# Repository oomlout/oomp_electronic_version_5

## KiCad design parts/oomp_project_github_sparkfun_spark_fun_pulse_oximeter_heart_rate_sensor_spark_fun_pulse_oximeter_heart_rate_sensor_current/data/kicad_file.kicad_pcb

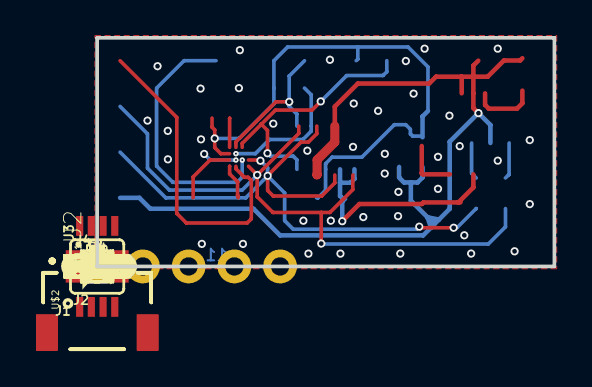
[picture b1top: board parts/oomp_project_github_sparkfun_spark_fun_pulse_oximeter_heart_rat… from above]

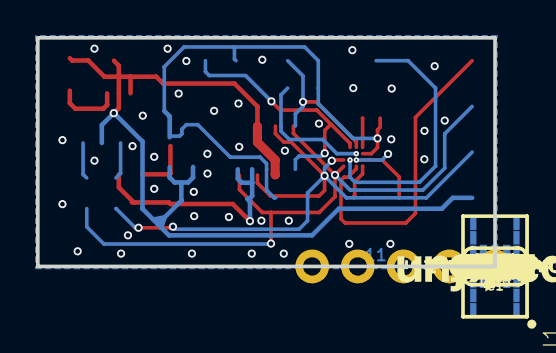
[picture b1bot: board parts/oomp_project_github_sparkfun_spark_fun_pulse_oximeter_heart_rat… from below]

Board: 2 copper layers, 25.4 x 12.7 mm, 50 parts (24 on the bottom side), 18 nets.

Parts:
C1, C3: 10uF; 0603
C2: 0.1uF; 0402-TIGHT
C4: 22uF; 0805
C5: 1.0uF; 0603
C6, C7: 1.0uF; 0402-TIGHT
FD1, FD2, FD3, FD4: FIDUCIALUFIDUCIAL; FIDUCIAL-MICRO
FRAME1: FRAME-LETTER; CREATIVE_COMMONS
I2C0: JUMPER-SMT_3_2-NC_TRACE_SILK; SMT-JUMPER_3_2-NC_TRACE_SILK
J1, J2: QWIIC_RIGHT_ANGLE; JST04_1MM_RA
J3: 1X05_NO_SILK
J4: 1X01_NO_SILK
L1: 2.2μH; 0806
LOGO1: SFE_LOGO_FLAME.1_INCH; SFE_LOGO_FLAME_.1
LOGO2: OSHW-LOGOMINI; OSHW-LOGO-MINI
LOGO3: SFE_LOGO_NAME.1_INCH; SFE_LOGO_NAME_.1
LOGO4: SPECIAL_INSTRUCTIONS-ORDERING; ORDERING_INSTRUCTIONS
LOGO5: QWIIC_LOGO_4MM; QWIIC_4MM
R1, R2, R5, R6, R7: 4.7k; 0603
R3: 750K; 0603
R4: 100k; 0402-TIGHT
U1: MAX30101EFD; 14_PIN_OESIP
U2: MAX32664GWEA; 16_PIN_WLP
U3: 1.8V/100mA; SC70
U$1: #I2C#1348
U$2: PAM2401; MSOP8
U$3, U$5: #GND#0
U$4: #SCL#7
U$6, U$12: #RST#32
U$7: 3V338
U$8: #SDA#10
U$9: #3V3#1
U$10: #SDA#9
U$11: #SCL#9
U$13: ##MFIO##12
U$17: PULSE35
U$20: OXIMETER_AND36
U$21: HEART_RATE_MONITOR37
Y1: 32.768kHz; CRYSTAL-SMD-3.2X1.5MM

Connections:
1.8V: C2.1, C5.1, C6.1, R1.2, R2.2, R5.2, U1.P11, U2.3, U3.5
3.3V: C3.1, I2C0.2, J1.2, J2.2, J3.2, L1.1, U3.1, U3.3, U$2.2, U$2.3
5V: C1.1, C4.1, R3.2, U1.P9, U1.P10, U$2.7
GND: C1.2, C2.2, C3.2, C4.2, C5.2, C6.2, C7.2, J1.1, J2.1, J3.1, R4.1, U1.P4, U1.P12, U2.13, U3.2, U$2.4, U$2.8
HOST_SCL: J1.4, J2.4, J3.4, R7.1, U2.10
HOST_SDA: J1.3, J2.3, J3.3, R6.1, U2.9
unnamed: C7.1, U2.4
unnamed: R3.1, R4.2, U$2.5
unnamed: L1.2, U$2.1
unnamed: I2C0.3, R6.2
unnamed: I2C0.1, R7.2
unnamed: U2.1, Y1.P$1
unnamed: U2.2, Y1.P$2
SNSR_SCL: R2.1, U1.P2, U2.5
SNSR_SDA: R1.1, U1.P3, U2.14
~HR_INT: R5.1, U1.P13, U2.6
~MFIO: J4.1, U2.16
~RST: J3.5, U2.12

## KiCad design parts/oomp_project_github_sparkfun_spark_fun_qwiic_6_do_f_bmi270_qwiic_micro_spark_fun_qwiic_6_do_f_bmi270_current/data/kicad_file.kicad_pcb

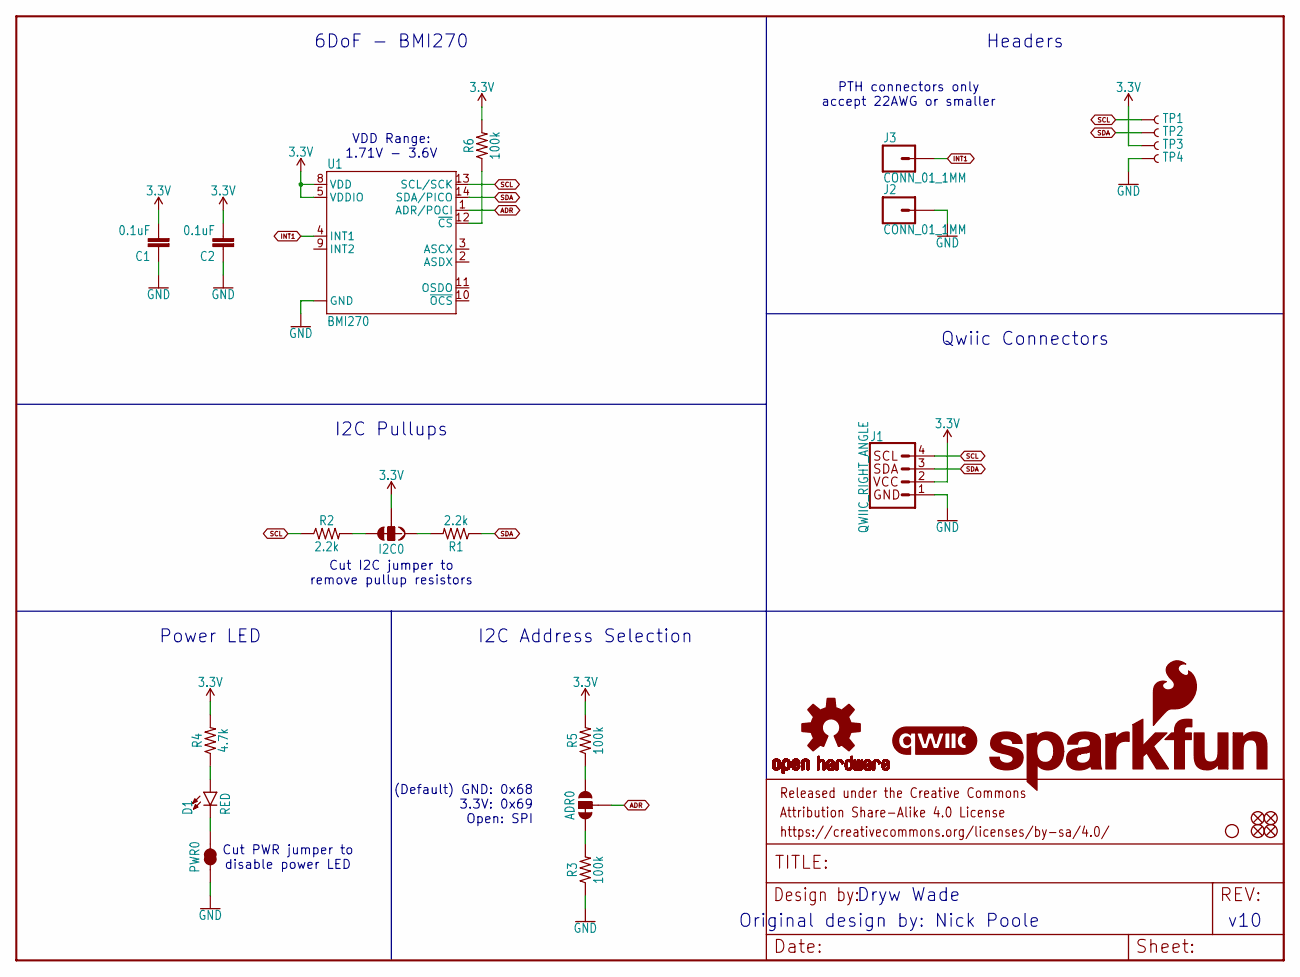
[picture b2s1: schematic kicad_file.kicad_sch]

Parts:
ADR0: JUMPER-SMT_3_1-NC_TRACE_SILK; SMT-JUMPER_3_1-NC_TRACE_SILK
C1, C2: 0.1uF; 0402-TIGHT
D1: RED; LED-0402
FD1, FD2, FD3, FD4: FIDUCIALUFIDUCIAL; FIDUCIAL-MICRO
FRAME1: FRAME-LETTER; CREATIVE_COMMONS
H1: STAND-OFF
I2C0: JUMPER-SMT_3_2-NC_TRACE_SILK; SMT-JUMPER_3_2-NC_TRACE_SILK
J1: QWIIC_RIGHT_ANGLE; JST04_1MM_RA
J2, J3: CONN_01_1MM; 1X01_1MM_NO_SILK
LOGO1: SFE_LOGO_NAME_FLAMEBLANK; BLANK
LOGO2: QWIIC_LOGO_3MM; QWIIC_3MM
LOGO3: OSHW-LOGOMINI; OSHW-LOGO-MINI
PWR0: JUMPER-SMT_2_NC_TRACE_SILK; SMT-JUMPER_2_NC_TRACE_SILK
R1, R2: 2.2k; 0402-TIGHT
R3, R5, R6: 100k; 0402-TIGHT
R4: 4.7k; 0402-TIGHT
TP1, TP2, TP3, TP4: TEST-POINT3; PAD.03X.03
U1: BMI270

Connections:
3.3V: C1.2, C2.2, I2C0.2, J1.2, R4.2, R5.2, R6.2, TP3.1, U1.5 (VDDIO), U1.8 (VDD)
ADR: ADR0.2, U1.1 (ADR/POCI)
GND: C1.1, C2.1, J1.1, J2.1, PWR0.1, R3.1, TP4.1, U1.6 (GND), U1.7 (GND)
INT1: J3.1, U1.4 (INT1)
unnamed: I2C0.1, R1.2
unnamed: I2C0.3, R2.2
unnamed: D1.C, PWR0.2
unnamed: D1.A, R4.1
unnamed: ADR0.1, R5.1
unnamed: ADR0.3, R3.2
unnamed: R6.1, U1.12 (~CS)
SCL: J1.4, R2.1, TP1.1, U1.13 (SCL/SCK)
SDA: J1.3, R1.1, TP2.1, U1.14 (SDA/PICO)

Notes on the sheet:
Qwiic Connectors
Power LED
I2C Pullups
Dryw Wade
v10
Original design by: Nick Poole
Cut I2C jumper to remove pullup resistors
Cut PWR jumper to disable power LED
6DoF - BMI270
I2C Address Selection
Headers
PTH connectors only accept 22AWG or smaller
VDD Range: 1.71V - 3.6V
(Default) GND: 0x68 3.3V: 0x69 Open: SPI

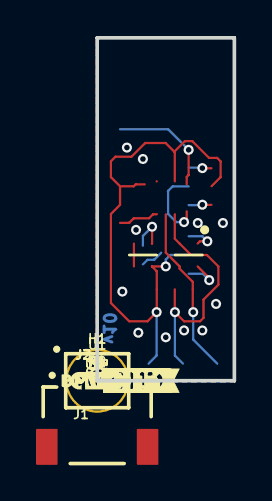
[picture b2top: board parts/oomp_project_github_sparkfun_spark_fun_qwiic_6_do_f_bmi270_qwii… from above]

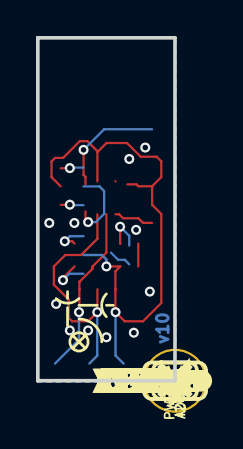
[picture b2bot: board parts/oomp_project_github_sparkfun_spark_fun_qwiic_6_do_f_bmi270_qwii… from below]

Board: 2 copper layers, 7.6 x 19.1 mm, 45 parts (22 on the bottom side), 13 nets.

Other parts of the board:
U$1: #I2C#0
U$2, U$7: #GND#0
U$3: SFE_LOGO_FLAME_.1
U$4: #PWR#0
U$5: #ADR#0
U$6: #0X68#0
U$8, U$9: #INT1#0
U$18: #0X69#0
U$21: BMI2700
U$33: ORDERING_INSTRUCTIONS
U$34: PWR0
U$79: X0
U$80: Y0
U$81: Z0

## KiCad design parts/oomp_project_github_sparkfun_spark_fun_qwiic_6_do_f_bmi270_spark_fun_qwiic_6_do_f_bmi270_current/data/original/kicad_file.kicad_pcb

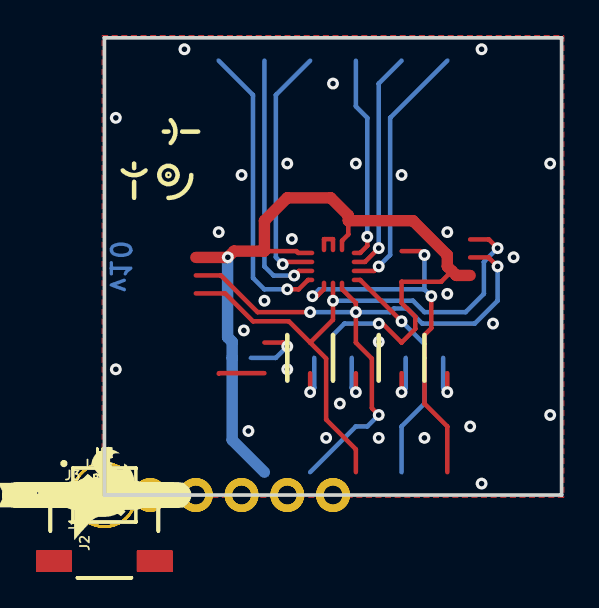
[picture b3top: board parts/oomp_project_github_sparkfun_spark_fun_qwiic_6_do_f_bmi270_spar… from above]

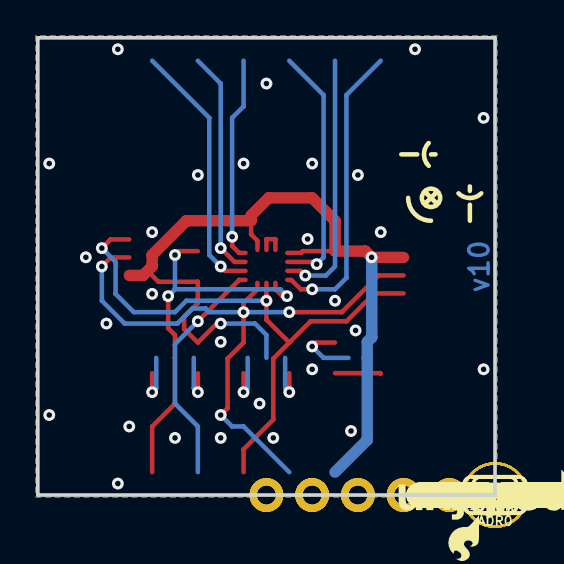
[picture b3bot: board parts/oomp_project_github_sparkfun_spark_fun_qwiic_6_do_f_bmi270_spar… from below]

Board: 2 copper layers, 25.4 x 25.4 mm, 69 parts (27 on the bottom side), 18 nets.

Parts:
ADR0: JUMPER-SMT_3_1-NC_TRACE_SILK; SMT-JUMPER_3_1-NC_TRACE_SILK
C1, C2: 0.1uF; 0603
D1: RED; LED-0603
FD1, FD2, FD3, FD4: FIDUCIAL1X2; FIDUCIAL-1X2
FRAME1: FRAME-LETTER; CREATIVE_COMMONS
H1, H2, H3, H4: STAND-OFF
I2C0: JUMPER-SMT_3_2-NC_TRACE_SILK; SMT-JUMPER_3_2-NC_TRACE_SILK
J1, J2: QWIIC_RIGHT_ANGLE; JST04_1MM_RA
J3, J4: 1X06_NO_SILK
LOGO1: SFE_LOGO_NAME_FLAME.1_INCH; SFE_LOGO_NAME_FLAME_.1
LOGO2: QWIIC_LOGO_5MM; QWIIC_5MM
LOGO3: OSHW-LOGOS; OSHW-LOGO-S
PWR0: JUMPER-SMT_2_NC_TRACE_SILK; SMT-JUMPER_2_NC_TRACE_SILK
R1, R2: 2.2k; 0603
R3, R5, R6: 100k; 0603
R4: 4.7k; 0603
U1: BMI270
U$1: #I2C#0
U$2, U$14: #_SDA#0
U$3: SFE_LOGO_FLAME_.2
U$4: #PWR#0
U$5: #ADR#0
U$6: #0X68#0
U$7, U$13: #_3V3#0
U$8, U$17: #_#CS##0
U$9, U$16: #_ADR#0
U$10, U$15: #_SCL#0
U$11, U$27: #ASDX_#0
U$12, U$19: #_GND#0
U$18: #0X69#0
U$20, U$21: BMI2700
U$22, U$28: #ASCX_#0
U$23, U$29: #INT1_#0
U$24, U$30: #INT2_#0
U$25, U$31: ##OCS#_#0
U$26, U$32: #OSDO_#0
U$33: ORDERING_INSTRUCTIONS
U$34: PWR0
U$79, U$88: X0
U$80, U$89: Y0
U$81, U$90: Z0

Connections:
3.3V: C1.2, C2.2, I2C0.2, J1.2, J2.2, J4.2, PWR0.2, R5.2, R6.2, U1.5, U1.8
ADR/POCI: ADR0.2, J4.5, U1.1
ASCX: J3.2, U1.3
ASDX: J3.1, U1.2
GND: C1.1, C2.1, D1.C, J1.1, J2.1, J4.1, R3.1, U1.6, U1.7
INT1: J3.3, U1.4
INT2: J3.4, U1.9
unnamed: I2C0.1, R1.2
unnamed: I2C0.3, R2.2
unnamed: PWR0.1, R4.2
unnamed: D1.A, R4.1
unnamed: ADR0.1, R5.1
unnamed: ADR0.3, R3.2
OSDO: J3.6, U1.11
SCL/SCK: J1.4, J2.4, J4.4, R2.1, U1.13
SDA/PICO: J1.3, J2.3, J4.3, R1.1, U1.14
~CS: J4.6, R6.1, U1.12
~OCS: J3.5, U1.10

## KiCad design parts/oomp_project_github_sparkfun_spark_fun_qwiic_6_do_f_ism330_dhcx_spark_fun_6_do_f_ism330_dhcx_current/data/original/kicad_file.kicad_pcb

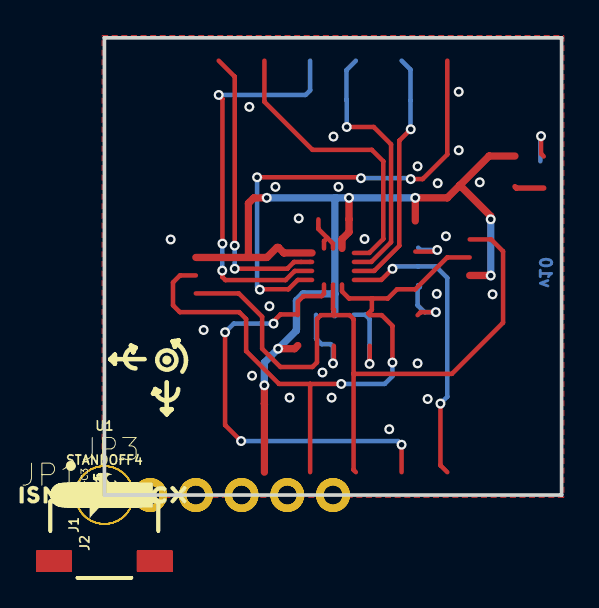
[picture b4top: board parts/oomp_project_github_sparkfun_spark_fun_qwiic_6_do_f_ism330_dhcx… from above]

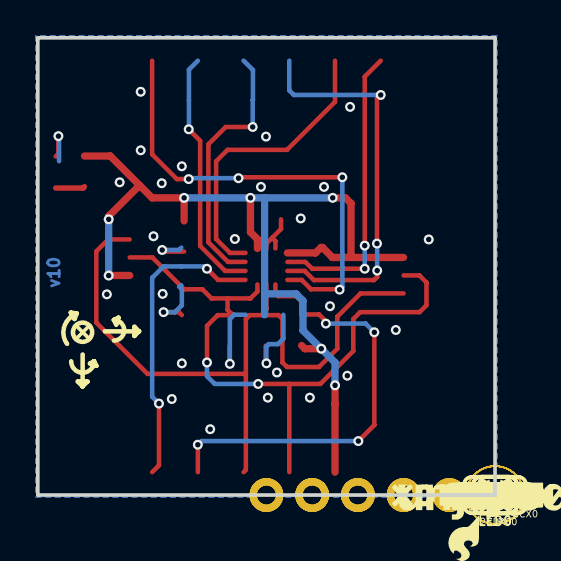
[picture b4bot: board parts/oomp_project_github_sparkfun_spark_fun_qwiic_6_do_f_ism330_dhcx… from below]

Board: 2 copper layers, 25.4 x 25.4 mm, 70 parts (30 on the bottom side), 18 nets.

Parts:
ADDR0: JUMPER-SMT_3_1-NC_TRACE_SILK; SMT-JUMPER_3_1-NC_TRACE_SILK
C3, C4: 0.1uF; 0603
D1: RED; LED-0603
FD1, FD2: FIDUCIALUFIDUCIAL; FIDUCIAL-MICRO
FID1, FID2: FIDUCIALUFIDUCIAL; FIDUCIAL-MICRO
FRAME1: FRAME-LETTER; CREATIVE_COMMONS
I2C_PU0: S_MODE; SMT-JUMPER_3_2-NC_TRACE_SILK
J1, J2: QWIIC_RIGHT_ANGLE; JST04_1MM_RA
JP1, JP3: IO; 1X06_NO_SILK
LED0: JUMPER-SMT_2_NC_TRACE_SILK; SMT-JUMPER_2_NC_TRACE_SILK
LOGO1: QWIIC_LOGO_4MM; QWIIC_4MM
LOGO2: OSHW-LOGOMINI; OSHW-LOGO-MINI
LOGO3: SFE_LOGO_NAME_FLAME.1_INCH; SFE_LOGO_NAME_FLAME_.1
R1, R2: 2.2k; 0603
R3, R5, R6: 10k; 0603
R4: 1k; 0603
SCX0: JUMPER-SMT_2_NC_TRACE_SILK; SMT-JUMPER_2_NC_TRACE_SILK
SDX0: JUMPER-SMT_2_NC_TRACE_SILK; SMT-JUMPER_2_NC_TRACE_SILK
STANDOFF1, STANDOFF2, STANDOFF3, STANDOFF4: STAND-OFFTIGHT; STAND-OFF-TIGHT
U1: ISM330DHCX; LGA-14L
U$1, U$15: #3V3#1
U$2, U$17: #GND#0
U$3: ##CS##7
U$4: #SDA#4
U$5, U$22: #SCL#5
U$6: #POCI#11
U$7, U$19: #INT1#9
U$8: #INT2#2
U$9: #OCS#8
U$10: #SCX#9
U$11: #PICOX#10
U$12: ISM330DHCX331
U$13: #0X6A#11
U$14: #0X6B#11
U$16: #LED#11
U$18: #POCI#12
U$20: #OCS#7
U$23: #SCX#8
U$24: #POCIX#8
U$25: #I2C#11
U$26: #PICO#13
U$27: ##CS##8
U$28: PWR8
U$29: SFE_LOGO_FLAME_.1
U$30: ISM330DHCX20
U$31: 6DOF12
U$32: #PICOX#9
U$33: #POCIX#7
U$34, U$37: X2114
U$35, U$38: Y2115
U$36, U$39: Z2116
U$40: #INT2#3

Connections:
3.3V: C3.1, C4.1, I2C_PU0.2, J1.2, J2.2, JP1.5, R3.2, R4.2, R5.2, U1.P5, U1.P8
GND: C3.2, C4.2, J1.1, J2.1, JP1.6, LED0.1, R6.1, SCX0.1, SDX0.1, U1.P6, U1.P7
INT1: JP3.2, U1.P4
INT2: JP3.1, U1.P9
unnamed: ADDR0.3, R5.1
unnamed: D1.A, R4.1
unnamed: D1.C, LED0.2
unnamed: I2C_PU0.1, R1.2
unnamed: I2C_PU0.3, R2.2
unnamed: ADDR0.1, R6.2
OCS: JP3.3, U1.P10
PICO_AUX: JP3.5, SDX0.2, U1.P2
POCI/SA0: ADDR0.2, JP1.1, U1.P1
POCI_AUX: JP3.6, U1.P11
SCL: J1.4, J2.4, JP1.3, R1.1, U1.P13
SCX: JP3.4, SCX0.2, U1.P3
SDA/PICO: J1.3, J2.3, JP1.4, R2.1, U1.P14
~CS: JP1.2, R3.1, U1.P12

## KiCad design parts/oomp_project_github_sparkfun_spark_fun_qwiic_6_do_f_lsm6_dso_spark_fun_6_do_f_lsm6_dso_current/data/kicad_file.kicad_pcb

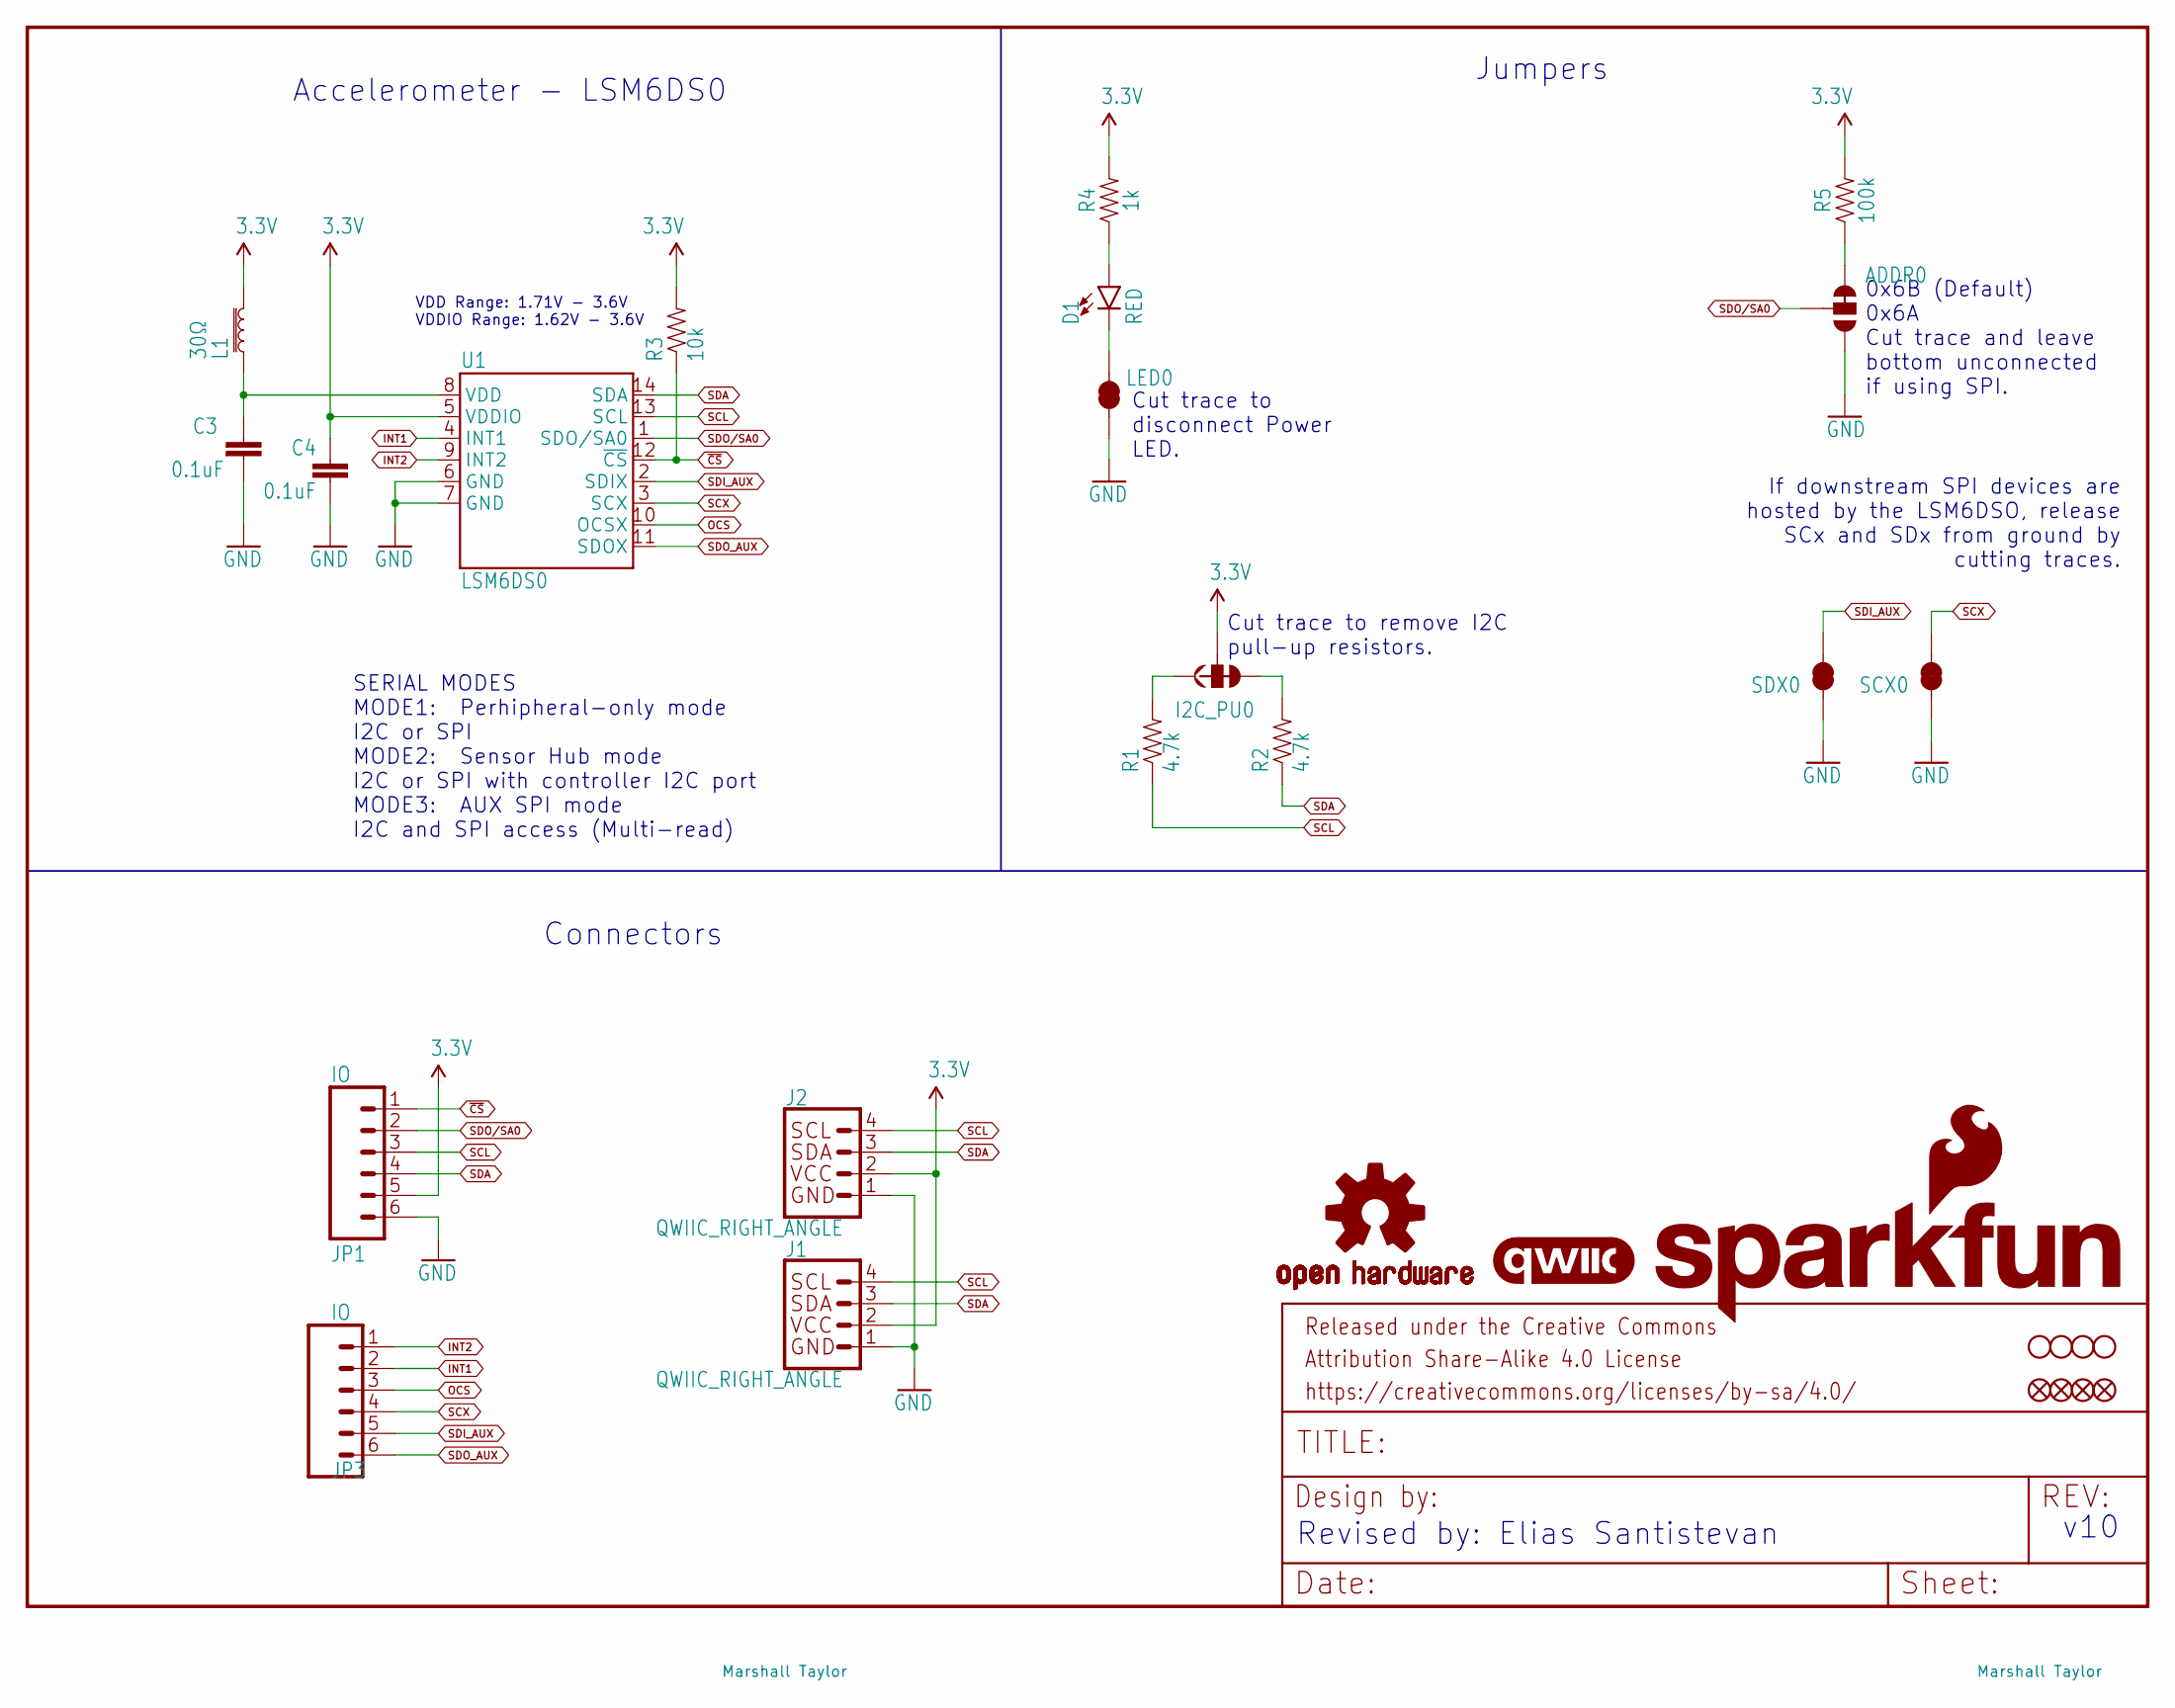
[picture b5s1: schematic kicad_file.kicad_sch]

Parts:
ADDR0: JUMPER-SMT_3_1-NC_TRACE_SILK; SMT-JUMPER_3_1-NC_TRACE_SILK
C3, C4: 0.1uF; 0603
D1: RED; LED-0603
FD1, FD2: FIDUCIALUFIDUCIAL; FIDUCIAL-MICRO
FID1, FID2: FIDUCIALUFIDUCIAL; FIDUCIAL-MICRO
FRAME1: FRAME-LETTER; CREATIVE_COMMONS
I2C_PU0: S_MODE; SMT-JUMPER_3_2-NC_TRACE_SILK
J1, J2: QWIIC_RIGHT_ANGLE; JST04_1MM_RA
JP1, JP3: IO; 1X06_NO_SILK
L1: 30Ω; 0603
LED0: JUMPER-SMT_2_NC_TRACE_SILK; SMT-JUMPER_2_NC_TRACE_SILK
LOGO1: QWIIC_LOGO_4MM; QWIIC_4MM
LOGO2: OSHW-LOGOS; OSHW-LOGO-S
LOGO3: SFE_LOGO_NAME_FLAME.1_INCH; SFE_LOGO_NAME_FLAME_.1
R1, R2: 4.7k; 0603
R3: 10k; 0603
R4: 1k; 0603
R5: 100k; 0603
SCX0: JUMPER-SMT_2_NC_TRACE_SILK; SMT-JUMPER_2_NC_TRACE_SILK
SDX0: JUMPER-SMT_2_NC_TRACE_SILK; SMT-JUMPER_2_NC_TRACE_SILK
STANDOFF1, STANDOFF2, STANDOFF3, STANDOFF4: STAND-OFFTIGHT; STAND-OFF-TIGHT
U1: LSM6DS0; LGA14L

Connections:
3.3V: C4.1, I2C_PU0.2, J1.2, J2.2, JP1.5, L1.1, R3.2, R4.2, R5.2, U1.5 (VDDIO)
GND: ADDR0.1, C3.2, C4.2, J1.1, J2.1, JP1.6, LED0.1, SCX0.1, SDX0.1, U1.6 (GND), U1.7 (GND)
INT1: JP3.2, U1.4 (INT1)
INT2: JP3.1, U1.9 (INT2)
unnamed: ADDR0.3, R5.1
unnamed: D1.A, R4.1
unnamed: D1.C, LED0.2
unnamed: I2C_PU0.1, R1.2
unnamed: I2C_PU0.3, R2.2
OCS: JP3.3, U1.10 (OCSX)
SCL: J1.4, J2.4, JP1.3, R1.1, U1.13 (SCL)
SCX: JP3.4, SCX0.2, U1.3 (SCX)
SDA: J1.3, J2.3, JP1.4, R2.1, U1.14 (SDA)
SDI_AUX: JP3.5, SDX0.2, U1.2 (SDIX)
SDO/SA0: ADDR0.2, JP1.2, U1.1 (SDO/SA0)
SDO_AUX: JP3.6, U1.11 (SDOX)
VDD: C3.1, L1.2, U1.8 (VDD)
~CS: JP1.1, R3.1, U1.12 (~CS)

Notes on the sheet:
Cut trace to remove I2C pull-up resistors.
0x6B (Default) 0x6A Cut trace and leave bottom unconnected if using SPI.
Cut trace to disconnect Power LED.
If downstream SPI devices are hosted by the LSM6DSO, release SCx and SDx from ground by cutting traces.
v10
Connectors
VDD Range: 1.71V - 3.6V VDDIO Range: 1.62V - 3.6V
SERIAL MODES MODE1: Perhipheral-only mode I2C or SPI MODE2: Sensor Hub mode I2C or SPI with controller I2C port MODE3: AUX SPI mode I2C and SPI access (Multi-read)
Revised by: Elias Santistevan
Accelerometer - LSM6DS0
Jumpers

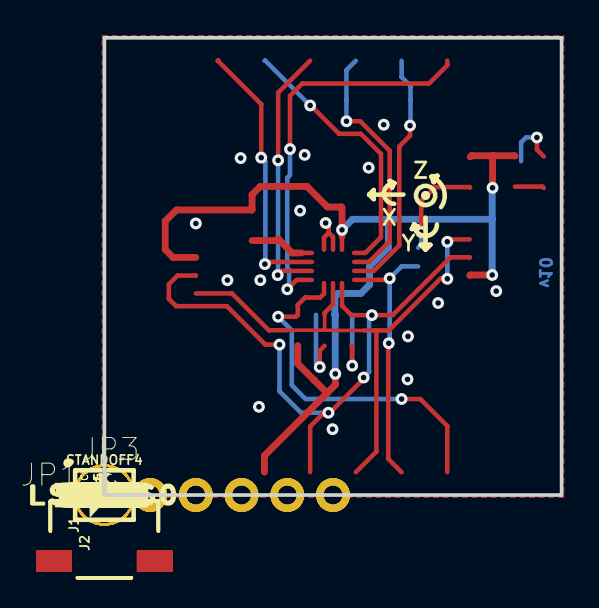
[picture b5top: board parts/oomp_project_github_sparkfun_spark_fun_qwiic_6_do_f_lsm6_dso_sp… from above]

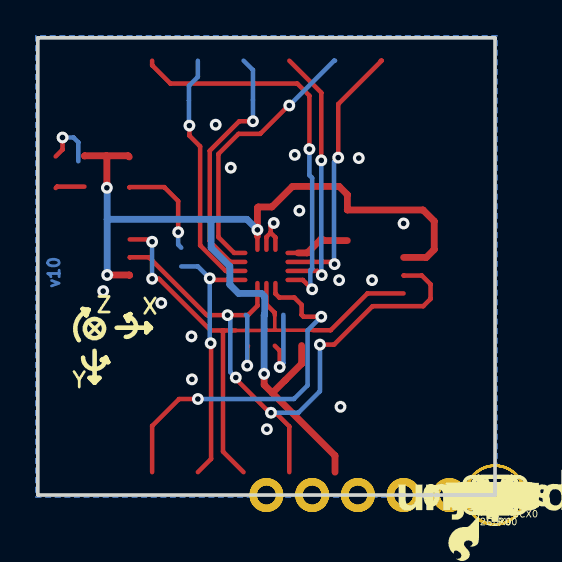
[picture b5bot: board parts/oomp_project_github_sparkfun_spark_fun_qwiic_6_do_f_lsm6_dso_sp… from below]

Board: 2 copper layers, 25.4 x 25.4 mm, 64 parts (27 on the bottom side), 18 nets.

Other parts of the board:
U$1, U$15: #3V3#1
U$2, U$17: #GND#0
U$3: ##CS##7
U$4: #SDA#4
U$5, U$22: #SCL#5
U$6: #SDO#6
U$7, U$19: #INT1#9
U$8, U$21: #INT2#9
U$9: #OCS#8
U$10: #SCX#9
U$11, U$33: #SDIX#11
U$12, U$30: LSM6DS011
U$13: #0X6A#11
U$14: #0X6B#11
U$16: #LED#11
U$18: #SDO#7
U$20: #OCS#7
U$23: #SCX#8
U$24, U$32: #SDOX#12
U$25: #I2C#11
U$26: #SDI#4
U$27: ##CS##8
U$28: PWR8
U$29: SFE_LOGO_FLAME_.1
U$31: 6DOF12

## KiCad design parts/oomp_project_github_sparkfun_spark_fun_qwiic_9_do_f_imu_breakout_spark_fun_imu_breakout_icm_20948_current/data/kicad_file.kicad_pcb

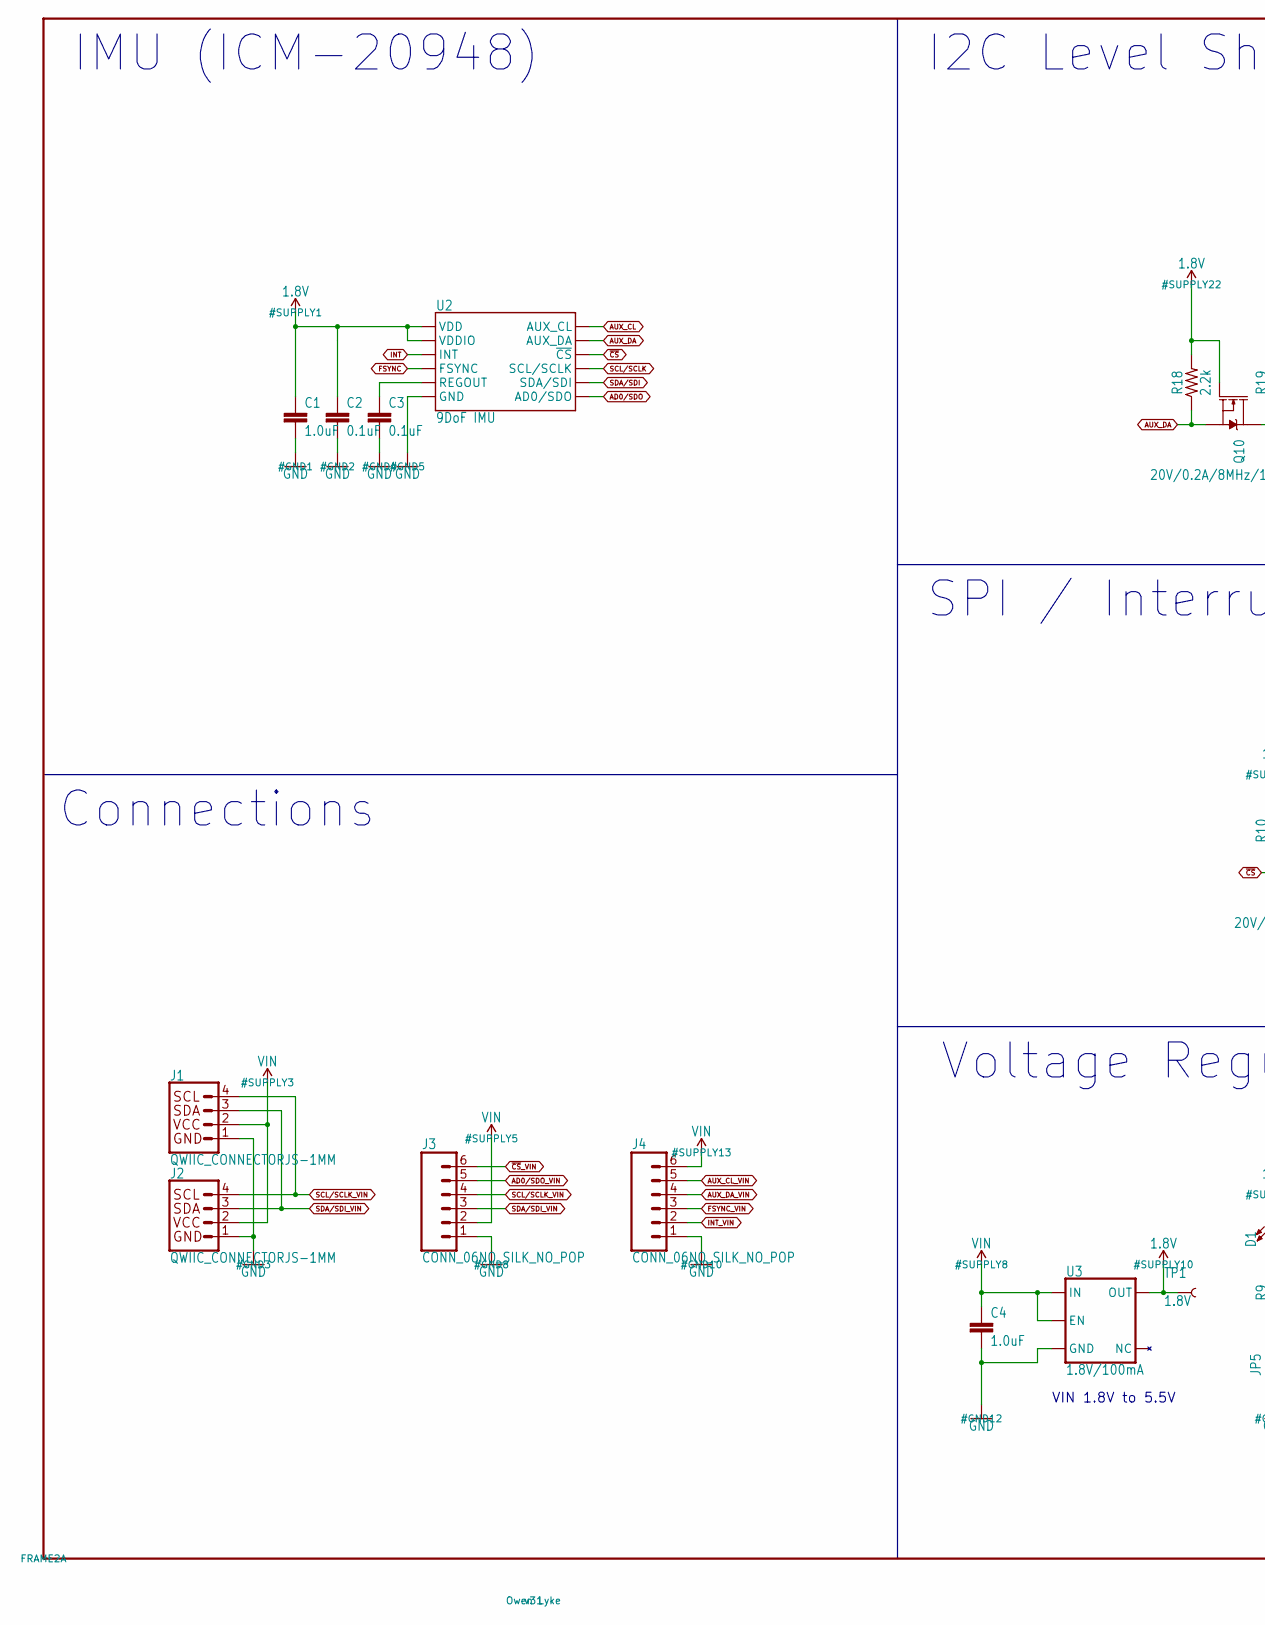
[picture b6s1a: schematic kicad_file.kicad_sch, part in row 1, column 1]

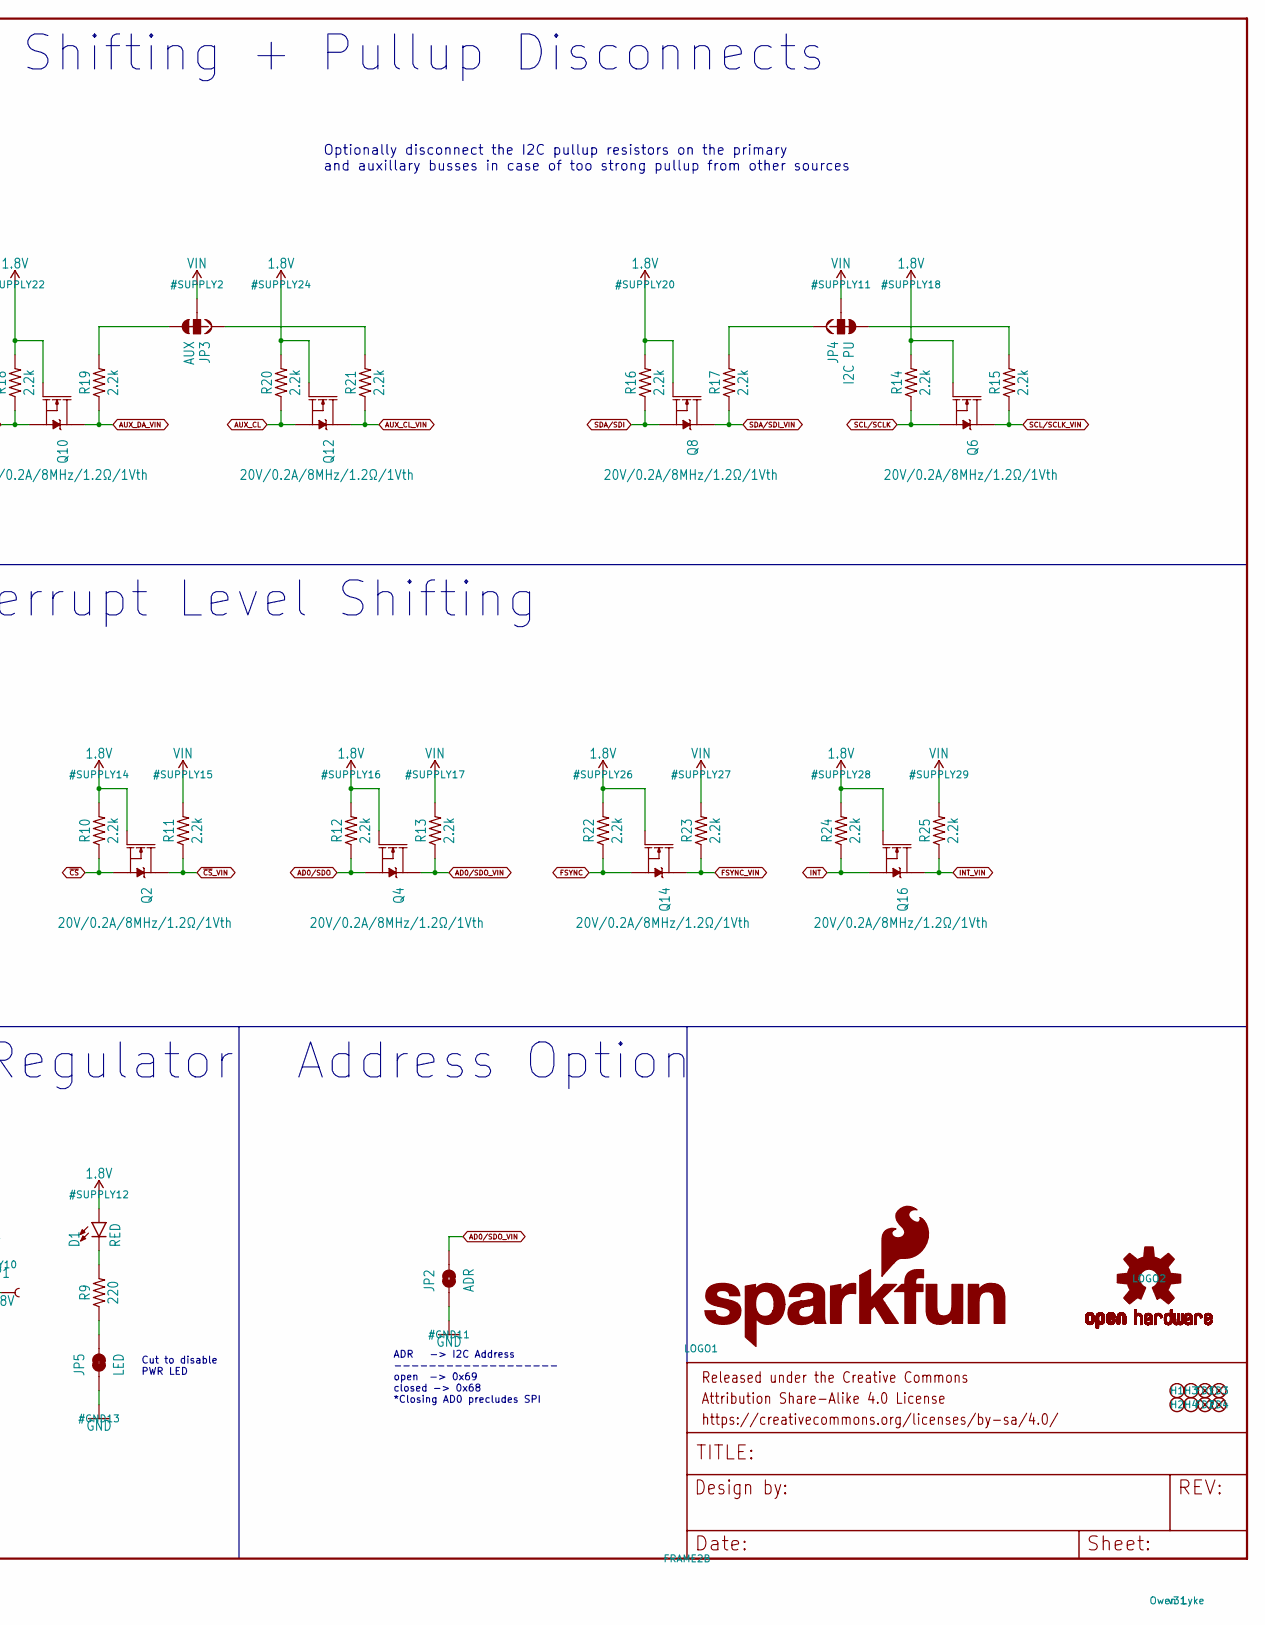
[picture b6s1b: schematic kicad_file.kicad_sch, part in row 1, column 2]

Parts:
C1, C4: 1.0uF; 0603
C2, C3: 0.1uF; 0603
D1: RED; LED-0603
FD1, FD2, FD3, FD4: FIDUCIAL1X2; FIDUCIAL-1X2
FRAME2: FRAME-LEDGER; CREATIVE_COMMONS
H1, H2, H3, H4: STAND-OFF
J1, J2: QWIIC_CONNECTORJS-1MM; JST04_1MM_RA
J3, J4: CONN_06NO_SILK_NO_POP; 1X06_NO_SILK
JP2: ADR; SMT-JUMPER_2_NO_SILK
JP3: AUX; SMT-JUMPER_3_2-NC_TRACE_SILK
JP4: I2C PU; SMT-JUMPER_3_2-NC_TRACE_SILK
JP5: LED; SMT-JUMPER_2_NC_TRACE_SILK
LOGO1: SFE_LOGO_NAME_FLAME.1_INCH; SFE_LOGO_NAME_FLAME_.1
LOGO2: OSHW-LOGOMINI; OSHW-LOGO-MINI
Q2, Q4, Q6, Q8, Q10, Q12, Q14, Q16: 20V/0.2A/8MHz/1.2Ω/1Vth; SOT-416FL
R9: 220; 0603
R10, R11, R12, R13, R14, R15, R16, R17, R18, R19, R20, R21, R22, R23, R24, R25: 2.2k; 0402-TIGHT
TP1: 1.8V; PAD.03X.03
U2: 9DoF IMU; QFN24-3X3
U3: 1.8V/100mA; SC70

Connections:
1.8V: C1.1, C2.1, D1.A, Q2.1 (G), Q4.1 (G), Q6.1 (G), Q8.1 (G), Q10.1 (G), Q12.1 (G), Q14.1 (G), Q16.1 (G), R10.2, R12.2, R14.2, R16.2, R18.2, R20.2, R22.2, R24.2, TP1.P$1, U2.8 (VDDIO), U2.13 (VDD), U3.5 (OUT)
AD0/SDO: Q4.2 (S), R12.1, U2.9 (AD0/SDO)
AD0/SDO_VIN: J3.5, JP2.2, Q4.3 (D), R13.1
AUX_CL: Q12.2 (S), R20.1, U2.7 (AUX_CL)
AUX_CL_VIN: J4.5, Q12.3 (D), R21.1
AUX_DA: Q10.2 (S), R18.1, U2.21 (AUX_DA)
AUX_DA_VIN: J4.4, Q10.3 (D), R19.1
FSYNC: Q14.2 (S), R22.1, U2.11 (FSYNC)
FSYNC_VIN: J4.3, Q14.3 (D), R23.1
GND: C1.2, C2.2, C3.2, C4.2, J1.1, J2.1, J3.1, J4.1, JP2.1, JP5.1, U2.18 (GND), U2.20 (GND), U3.2 (GND)
INT: Q16.2 (S), R24.1, U2.12 (INT)
INT_VIN: J4.2, Q16.3 (D), R25.1
unnamed: C3.1, U2.10 (REGOUT)
unnamed: JP4.3, R15.2
unnamed: JP4.1, R17.2
unnamed: JP3.1, R21.2
unnamed: JP3.3, R19.2
unnamed: D1.C, R9.2
unnamed: JP5.2, R9.1
SCL/SCLK: Q6.2 (S), R14.1, U2.23 (SCL/SCLK)
SCL/SCLK_VIN: J1.4, J2.4, J3.4, Q6.3 (D), R15.1
SDA/SDI: Q8.2 (S), R16.1, U2.24 (SDA/SDI)
SDA/SDI_VIN: J1.3, J2.3, J3.3, Q8.3 (D), R17.1
VIN: C4.1, J1.2, J2.2, J3.2, J4.6, JP3.2, JP4.2, R11.2, R13.2, R23.2, R25.2, U3.1 (IN), U3.3 (EN)
~CS: Q2.2 (S), R10.1, U2.22 (~CS)
~CS_VIN: J3.6, Q2.3 (D), R11.1

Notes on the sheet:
Connections
IMU (ICM-20948)
VIN 1.8V to 5.5V
Voltage Regulator
SPI / Interrupt Level Shifting
Cut to disable PWR LED
ADR -> I2C Address ------------------- open -> 0x69 closed -> 0x68 *Closing AD0 precludes SPI
I2C Level Shifting + Pullup Disconnects
Address Option
Optionally disconnect the I2C pullup resistors on the primary and auxillary busses in case of too strong pullup from other sources

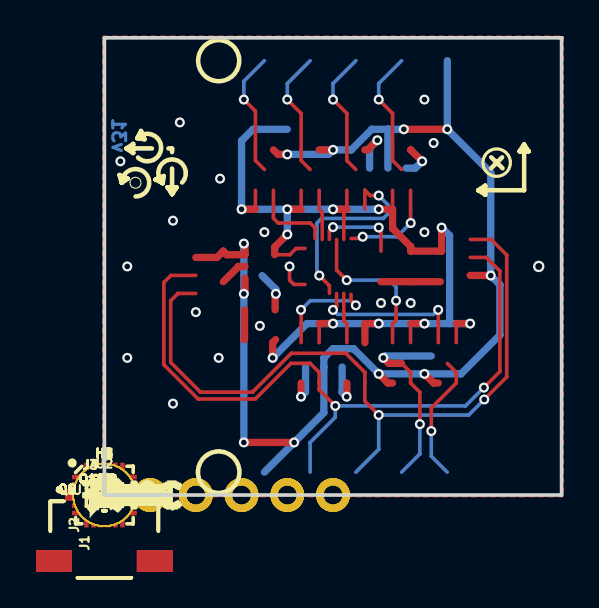
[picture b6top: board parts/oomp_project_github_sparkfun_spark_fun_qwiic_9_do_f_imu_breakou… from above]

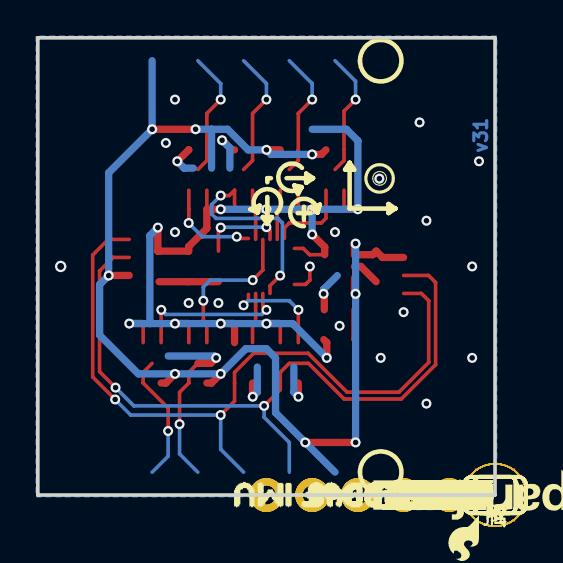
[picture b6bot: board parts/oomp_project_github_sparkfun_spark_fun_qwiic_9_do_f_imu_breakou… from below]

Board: 2 copper layers, 25.4 x 25.4 mm, 104 parts (36 on the bottom side), 26 nets.

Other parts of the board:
U$1, U$2, U$22, U$24: GND4
U$3: PWR0
U$4, U$21: INT3
U$5, U$20: FSNC2
U$6, U$19: ACL1
U$7, U$18: ADA0
U$8: MISO13
U$9: MOSI14
U$10: SCLK15
U$11: #CS16
U$12: 1V8#5V57
U$13, U$30, U$44: VIN5
U$14: NC17
U$15: CL4
U$16: DA2
U$17: AD012
U$23: ADR2
U$25: I2C_PU21
U$26: SPI19
U$27: AUX_PU24
U$28: SFE_LOGO_FLAME_.1
U$29: LED23
U$31: ICM#2094820
U$34, U$40, U$50, U$57: X0
U$35, U$41, U$51, U$58: Y1
U$36, U$42, U$52, U$59: Z2
U$37, U$60: G5
U$38, U$61: A4
U$39, U$49: M3
U$43: QWIIC_9DOF_IMU_0
U$45: I#C1

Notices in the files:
parts/oomp_project_github_sparkfun_spark_fun_qwiic_6_do_f_bmi270_qwiic_micro_spark_fun_qwiic_6_do_f_bmi270_current/data/original/kicad_file.kicad_sch:
Released under the Creative Commons
https://creativecommons.org/licenses/by-sa/4.0
parts and their libraries:
Released under the Creative Commons Attribution Share-Alike 4.0 License
